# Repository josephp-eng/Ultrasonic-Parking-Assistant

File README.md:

# STM32 Ultrasonic Parking Assistant
**Author:** Joseph Pokuta

**Course:** Embedded Microcontrollers (EE3174) | Michigan Technological University

**Date:** 12/03/25

This project implements a real-time distance-sensing parking aid designed for the STM32L152RE (ARM Cortex-M3) platform. The system provides immediate visual and auditory feedback to assist drivers in obstructed or low-visibility environments. It was developed as a complete embedded solution, spanning from initial KiCad schematic design to a hand-soldered hardware prototype.

Uses buzzers, lights, an LCD screen, and an ultrasonic sensor to provide a simple yet effective reverse-parking assistant.

*This project was completed for my Embedded Microcontrollers class at Michigan Tech. Be aware that the project files are named with 'EE3174' and 'JP' exactly how they were submitted for the class.*

## System Capabilities
* **Dynamic Range Calibration:** A 10k potentiometer is polled via ADC1 to set the "STOP" distance threshold (20cm - 150cm) in real time.
* **Signal Conditioning:** Implements a median-of-3 filter to eliminate ultrasonic sensor noise and software hysteresis to prevent LED/LCD flickering at band boundaries.
* **Contextual User Interface:** A single interrupt-driven button supports short-press (Mute) and long-press (System Enable/Disable) actions.
* **Non-Blocking Logic:** The buzzer PWM and LCD I2C updates are managed via state-machine logic to ensure the system remains responsive without utilizing CPU-halting delays.

| State | Visual | Description |
| :--- | :--- | :--- |
| **Out of Range (OOR)** |  | Active when objects are >60cm away. The system enters a low-activity state to prevent needless power draw and noise. |
| **Optimal Stop** |  | Indicates the vehicle has reached the precise "Stop" distance (e.g., 20cm) as calibrated by the user via the potentiometer. |

## Hardware Spec
The hardware was designed in KiCad and hand-soldered onto a protoboard shield.

[Hardware Schematic](Media/project_layout.jpg)

### Pin Mapping
| Peripheral | STM32 Pin | Mode | Purpose |
| :--- | :--- | :--- | :--- |
| **HC-SR04 Echo** | PA0 | TIM2 Input Capture | Measures pulse width for distance calculation |
| **HC-SR04 Trig** | PA9 | GPIO Output | Generates 12us trigger pulse |
| **I2C LCD** | PB8 / PB9 | I2C1 | Interface for MCP23008 Port Expander |
| **RGB LED** | PB13 - PB15 | GPIO Output | Tri-color visual proximity indicator |
| **Buzzer** | PB4 | TIM3 CH1 (PWM) | Variable frequency audio feedback |
| **Potentiometer** | PA4 | ADC1 | Real-time "Stop" threshold calibration |
| **User Button** | PA8 | EXTI (Interrupt) | Short press: Mute / Long press: Power |

### Bill of Materials
* 1x STM32L152RE Nucleo-64
* 1x HC-SR04 Ultrasonic Sensor
* 1x 16x2 Character LCD (I2C)
* 1x Common-Anode RGB LED
* 1x Piezo Buzzer
* 1x 10k Ohm Potentiometer
* 1x Momentary Tactile Switch
* 1x Protoboard Shield

## Challenges and Debugging
The transition from schematic to a soldered prototype involved significant hardware troubleshooting:
* **Voltage Rail Optimization:** Initial smoke testing revealed that the HC-SR04 and I2C LCD were underperforming on the 3.3V rail. The power domain was shifted to 5V while maintaining logic compatibility with the STM32's 5V-tolerant pins, resulting in stable sensor pings and clear LCD contrast.
* **Hardware Isolation:** A grounding failure on the piezo buzzer was identified late in the assembly phase. By isolating the buzzer subsystem and performing continuity tests, the fault was traced to a cold solder joint on the common ground plane and rectified.
* **OOR Logic:** Specialized handling was implemented for Out-of-Range measurements to prevent the system from reporting "ghost" distances or running the UI unnecessarily when the path is clear.

### Logic Flow
```mermaid
graph TD
    A[Start] --> B[Initialize Peripherals]
    B --> C[Self-Test: Buzzer Chirp]
    C --> D[Loop]
    D --> E[Read ADC: Update Stop Threshold]
    E --> F[Trigger HC-SR04 Sensor]
    F --> G[TIM2 Capture: Pulse Calculation]
    G --> H[Apply Median Filter & Hysteresis]
    H --> I{Distance Analysis}
    I --> J[Update RGB LED & Buzzer PWM]
    J --> K[Update LCD Cache]
    K --> D
```

## How to Run

### Hardware
* Wire the components according the to **Pin Mapping** table and the KiCad schematic `project_layout.jpg`
* Connect the STM32 Nucleo-64 board via Mini-USB to your device

### Software
* Open **STM32CubeIDE**.
* Import the project from the `/final_parkingAssistant_JP` directory.
* Open the `.ioc` file to verify the Clock Configuration (ensure the HCLK is set correctly for the Timer prescalers).
* Build the project to generate the `.elf` or `.bin` file.
* Connect your Nucleo board and click **Run** to flash the firmware.

### Usage
* Upon startup, the system will perform a short buzzer "chirp" to confirm the PWM and Piezo are functional.
* Adjust the **Potentiometer** to set your desired stopping distance.
* Use the **Button** to toggle the mute state ('M') or long-press to enter standby mode.

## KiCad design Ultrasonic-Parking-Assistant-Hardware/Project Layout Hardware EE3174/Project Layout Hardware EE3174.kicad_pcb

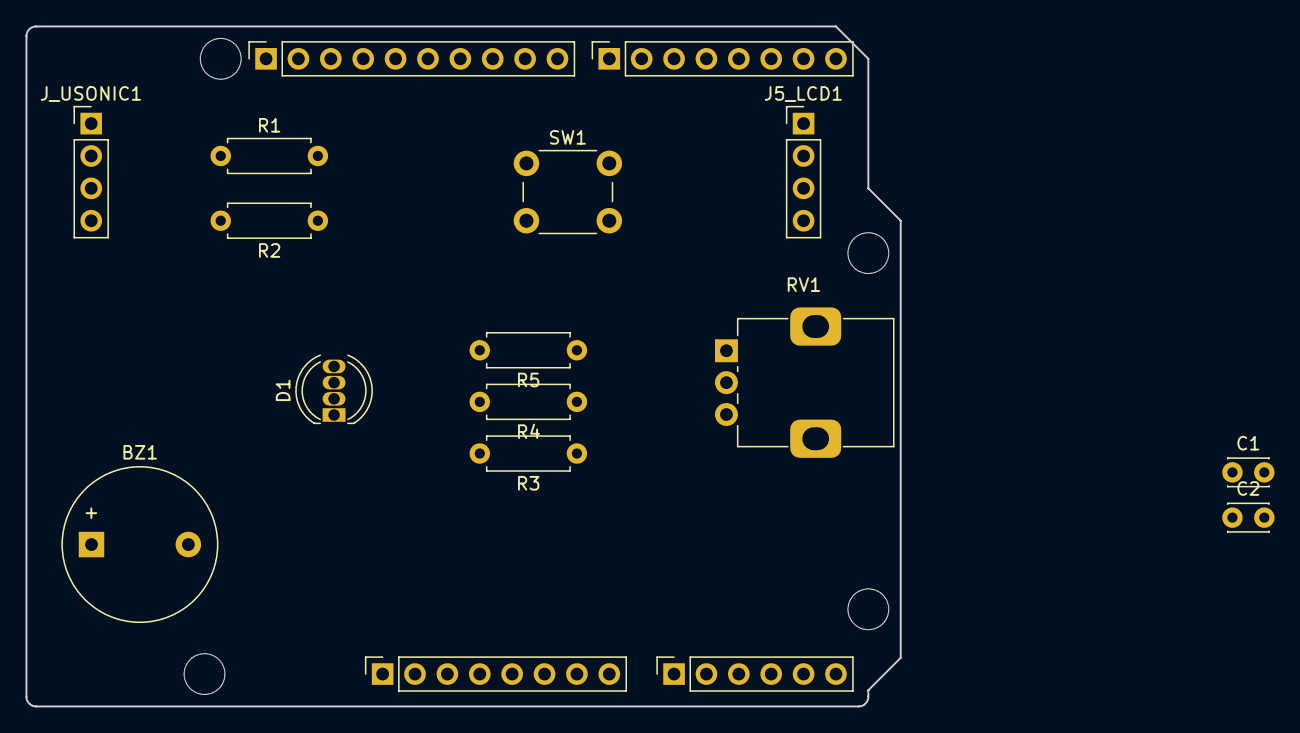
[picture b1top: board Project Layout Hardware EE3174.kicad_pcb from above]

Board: 2 copper layers, 68.6 x 53.3 mm, 21 parts (0 on the bottom side), 17 nets, no tracks yet.

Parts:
BZ1: Buzzer; Buzzer_12x9.5RM7.6
C1, C2: 0.1uF; C_Disc_D3.0mm_W2.0mm_P2.50mm
D1: LED_RGBA; LED_D5.0mm-4_RGB
J1: Power; PinSocket_1x08_P2.54mm_Vertical
J2: Digital/PWM; PinSocket_1x10_P2.54mm_Vertical
J3: Analog; PinSocket_1x06_P2.54mm_Vertical
J4: Digital/PWM; PinSocket_1x08_P2.54mm_Vertical
J5_LCD1: LCD_I2C; PinHeader_1x04_P2.54mm_Vertical
J_USONIC1: HC-SR04; PinHeader_1x04_P2.54mm_Vertical
MH1, MH2, MH3, MH4: MountingHole_3.2mm
R1: 20k; R_Axial_DIN0207_L6.3mm_D2.5mm_P7.62mm_Horizontal
R2: 10k; R_Axial_DIN0207_L6.3mm_D2.5mm_P7.62mm_Horizontal
R3, R4, R5: 330; R_Axial_DIN0207_L6.3mm_D2.5mm_P7.62mm_Horizontal
RV1: R_Potentiometer; Potentiometer_Alps_RK09K_Single_Vertical
SW1: SW_Push; SW_PUSH_6mm

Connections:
+3V3: D1.4 (A), J1.4, RV1.3
+5V: C1.1, C2.1, J1.5, J1.8, J5_LCD1.2, J_USONIC1.1 (VCC)
/2: J4.6, J_USONIC1.2 (TRIG)
/4: J4.4, R5.1
/7: J4.1, SW1.2
/12: BZ1.1 (+), J2.6
/*3: J4.5, R3.1
/*5: J4.3, R4.1
/A0: J3.1, R1.1, R2.1
/A2: J3.3, RV1.2
/ECHO_RAW: J_USONIC1.3 (ECHO), R1.2
/SCL: J2.1, J3.6, J5_LCD1.4
/SDA: J2.2, J3.5, J5_LCD1.3
GND: BZ1.2 (-), C1.2, C2.2, J1.6, J1.7, J2.4, J5_LCD1.1, J_USONIC1.4 (GND), R2.2, RV1.1, SW1.1
unnamed: D1.3 (BK), R5.2
unnamed: D1.2 (GK), R4.2
unnamed: D1.1 (RK), R3.2

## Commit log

2026-03-22 Upload Project
    Including STM32CubeIDE code and KiCad project files
2026-03-22 KiCad Update
2026-03-22 Create LICENSE
2026-03-22 KiCad Directory
2026-03-22 Extra Image files
2026-03-22 Fixing media
